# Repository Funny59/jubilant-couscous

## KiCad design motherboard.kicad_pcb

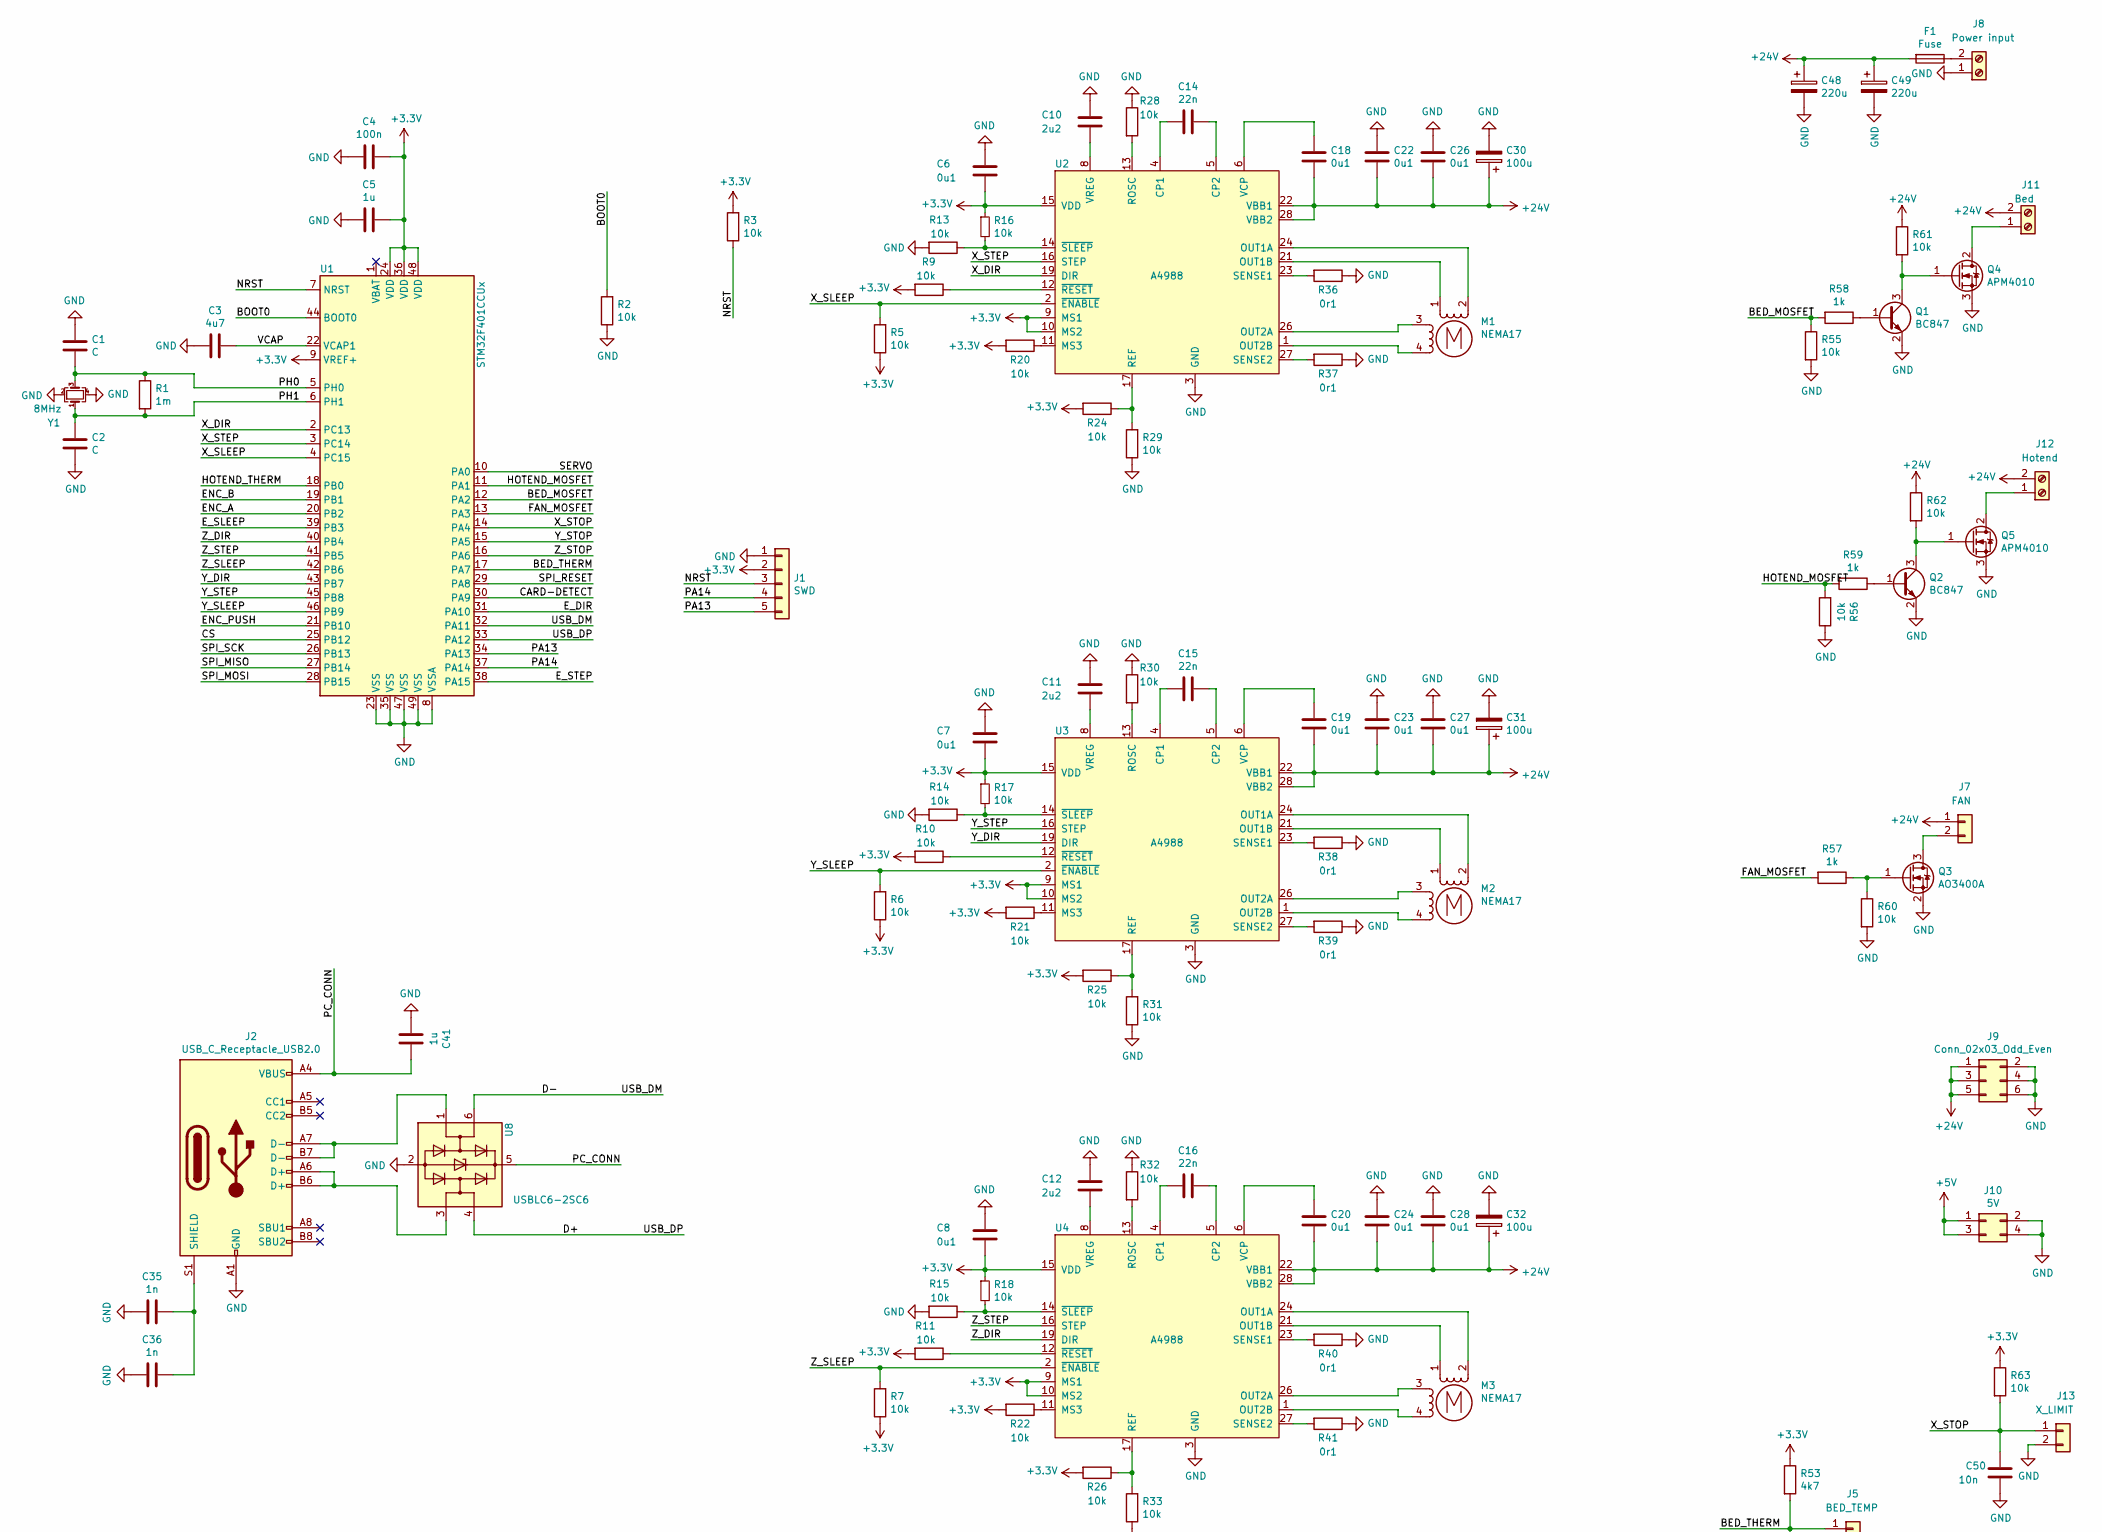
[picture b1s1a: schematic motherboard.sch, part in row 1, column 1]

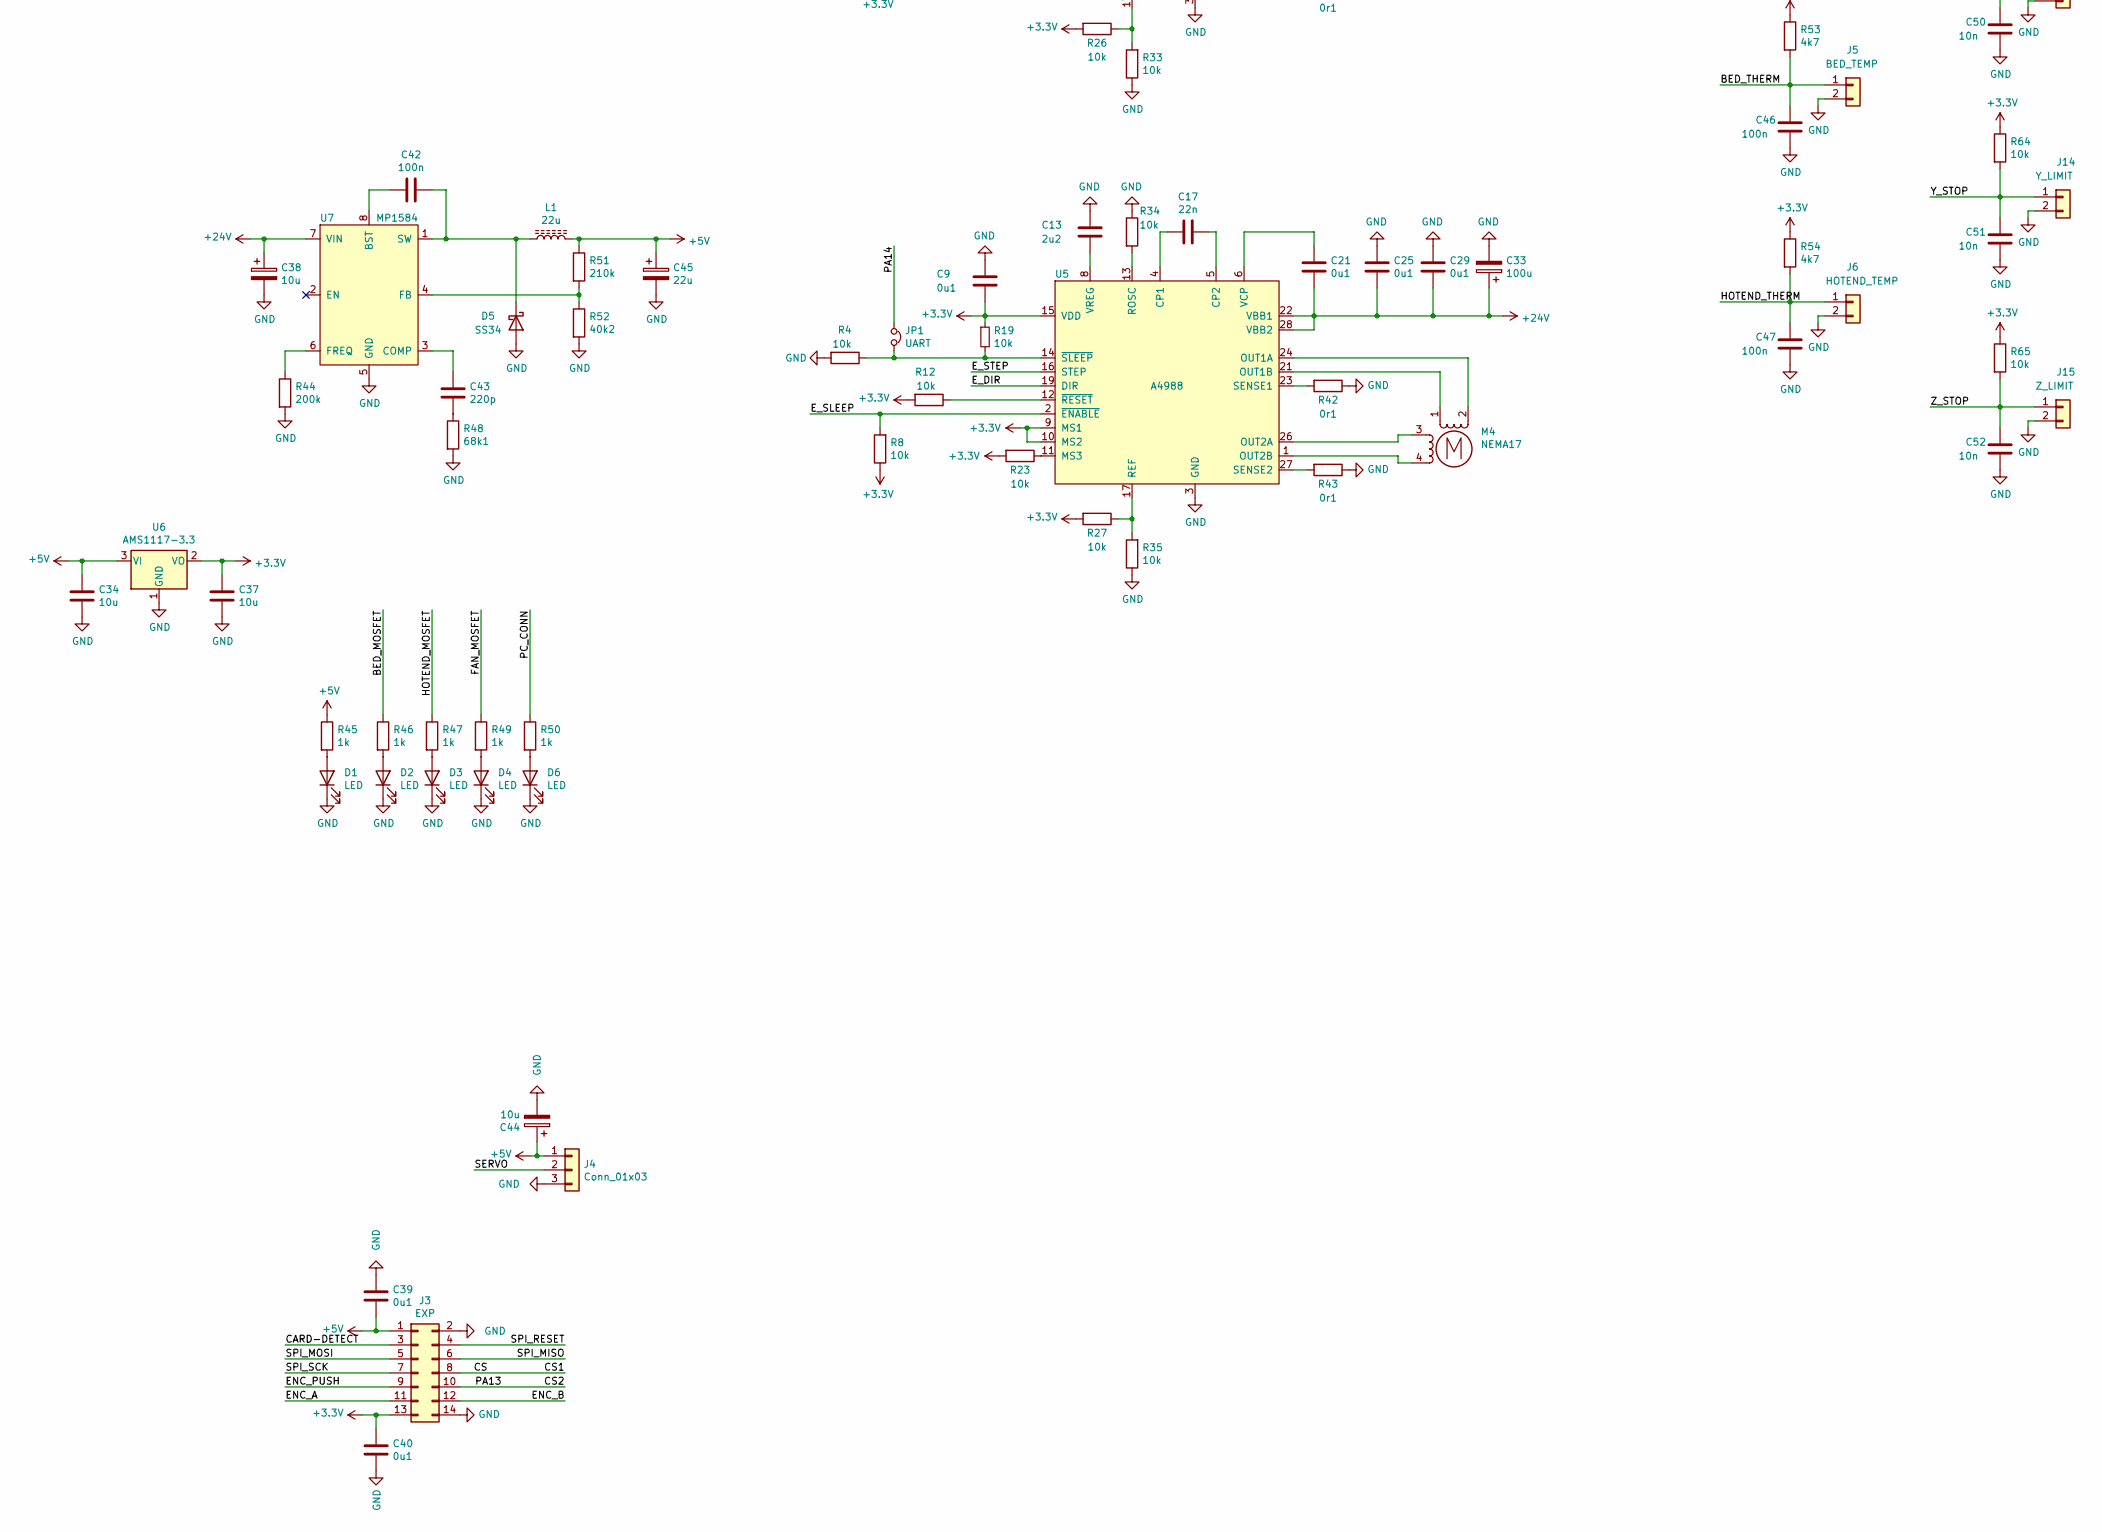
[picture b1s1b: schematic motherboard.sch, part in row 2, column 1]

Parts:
C1, C2: C; C_0603_1608Metric_Pad1.08x0.95mm_HandSolder
C3: 4u7; C_0603_1608Metric_Pad1.08x0.95mm_HandSolder
C4, C42, C46, C47: 100n; C_0603_1608Metric_Pad1.08x0.95mm_HandSolder
C5, C41: 1u; C_0603_1608Metric_Pad1.08x0.95mm_HandSolder
C6, C7, C8, C9, C18, C19, C20, C21, C22, C23, C24, C25, C26, C27, C28, C29, C39, C40: 0u1; C_0603_1608Metric_Pad1.08x0.95mm_HandSolder
C10, C11, C12, C13: 2u2; C_0603_1608Metric_Pad1.08x0.95mm_HandSolder
C14, C15, C16, C17: 22n; C_0603_1608Metric_Pad1.08x0.95mm_HandSolder
C30, C31, C32, C33: 100u; CP_Radial_D8.0mm_P3.50mm
C34, C37: 10u; C_0805_2012Metric_Pad1.18x1.45mm_HandSolder
C35, C36: 1n; C_0603_1608Metric_Pad1.08x0.95mm_HandSolder
C38, C44: 10u; CP_EIA-3528-21_Kemet-B_Pad1.50x2.35mm_HandSolder
C43: 220p; C_0603_1608Metric_Pad1.08x0.95mm_HandSolder
C45: 22u; CP_EIA-3528-21_Kemet-B_Pad1.50x2.35mm_HandSolder
C48, C49: 220u; CP_Radial_D8.0mm_P3.50mm
C50, C51, C52: 10n; C_0603_1608Metric_Pad1.08x0.95mm_HandSolder
D1, D2, D3, D4, D6: LED; LED_0603_1608Metric_Pad1.05x0.95mm_HandSolder
D5: SS34; D_SMA-SMB_Universal_Handsoldering
F1: Fuse; Fuse_Blade_Mini_directSolder
J1: SWD; PinHeader_1x05_P2.54mm_Vertical
J2: USB_C_Receptacle_USB2.0; USB_C_Receptacle_Palconn_UTC16-G
J3: EXP; IDC-Header_2x07_P2.54mm_Vertical
J4: Conn_01x03; JST_XH_B3B-XH-A_1x03_P2.50mm_Vertical
J5: BED_TEMP; JST_XH_B2B-XH-A_1x02_P2.50mm_Vertical
J6: HOTEND_TEMP; JST_XH_B2B-XH-A_1x02_P2.50mm_Vertical
J7: FAN; JST_XH_B2B-XH-A_1x02_P2.50mm_Vertical
J8: Power input; TerminalBlock_bornier-2_P5.08mm
J9: Conn_02x03_Odd_Even; PinHeader_2x03_P2.54mm_Vertical
J10: 5V; PinHeader_2x02_P2.54mm_Vertical
J11: Bed; TerminalBlock_bornier-2_P5.08mm
J12: Hotend; TerminalBlock_bornier-2_P5.08mm
J13: X_LIMIT; JST_XH_B2B-XH-A_1x02_P2.50mm_Vertical
J14: Y_LIMIT; JST_XH_B2B-XH-A_1x02_P2.50mm_Vertical
J15: Z_LIMIT; JST_XH_B2B-XH-A_1x02_P2.50mm_Vertical
JP1: UART; SolderJumper-2_P1.3mm_Open_TrianglePad1.0x1.5mm
L1: 22u; SDR0604
M1, M2, M3, M4: NEMA17; JST_XH_B4B-XH-A_1x04_P2.50mm_Vertical
Q1, Q2: BC847; SOT-23
Q3: AO3400A; SOT-23
Q4, Q5: APM4010; TO-252-2
R1: 1m; R_0603_1608Metric_Pad0.98x0.95mm_HandSolder
R2, R3, R24, R25, R26, R27, R55, R56, R60, R61, R62, R63, R64, R65: 10k; R_0603_1608Metric_Pad0.98x0.95mm_HandSolder
R4, R5, R6, R7, R8, R9, R10, R11, R12, R13, R14, R15, R16, R17, R18, R19, R20, R21, R22, R23, R28, R30, R32, R34: 10k; R_0402_1005Metric_Pad0.72x0.64mm_HandSolder
R29, R31, R33, R35: 10k; Potentiometer_Bourns_TC33X_Vertical
R36, R37, R38, R39, R40, R41, R42, R43: 0r1; R_1206_3216Metric_Pad1.30x1.75mm_HandSolder
R44: 200k; R_0603_1608Metric_Pad0.98x0.95mm_HandSolder
R45, R46, R47, R49, R50, R57, R58, R59: 1k; R_0603_1608Metric_Pad0.98x0.95mm_HandSolder
R48: 68k1; R_0603_1608Metric_Pad0.98x0.95mm_HandSolder
R51: 210k; R_0603_1608Metric_Pad0.98x0.95mm_HandSolder
R52: 40k2; R_0603_1608Metric_Pad0.98x0.95mm_HandSolder
R53, R54: 4k7; R_0603_1608Metric_Pad0.98x0.95mm_HandSolder
U1: STM32F401CCUx; QFN-48-1EP_7x7mm_P0.5mm_EP5.6x5.6mm
U2, U3, U4, U5: A4988; QFN-28-1EP_5x5mm_P0.5mm_EP3.35x3.35mm_ThermalVias
U6: AMS1117-3.3; SOT-223-3_TabPin2
U7: MP1584; SOIC-8-1EP_3.9x4.9mm_P1.27mm_EP2.29x3mm_ThermalVias
U8: USBLC6-2SC6; SOT-23-6
Y1: 8MHz; Crystal_SMD_3225-4Pin_3.2x2.5mm

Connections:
+3V3: C4.1, C5.1, C6.2, C7.2, C8.2, C9.2, C37.1, C40.2, J1.2, J3.13, R3.2, R5.1, R6.1, R7.1, R8.1, R9.2, R10.2, R11.2, R12.2, R16.1, R17.1, R18.1, R19.1, R20.2, R21.2, R22.2, R23.2, R24.2, R25.2, R26.2, R27.2, R53.1, R54.1, R63.1, R64.1, R65.1, U1.9 (VREF+), U1.24 (VDD), U1.36 (VDD), U1.48 (VDD), U2.9 (MS1), U2.10 (MS2), U2.15 (VDD), U3.9 (MS1), U3.10 (MS2), U3.15 (VDD), U4.9 (MS1), U4.10 (MS2), U4.15 (VDD), U5.9 (MS1), U5.10 (MS2), U5.15 (VDD), U6.2 (VO)
+5V: C34.1, C39.1, C44.1, C45.1, J3.1, J4.1, J10.1, J10.3, L1.2, R45.1, R51.1, U6.3 (VI)
+24V: C18.1, C19.1, C20.1, C21.1, C22.1, C23.1, C24.1, C25.1, C26.1, C27.1, C28.1, C29.1, C30.1, C31.1, C32.1, C33.1, C38.1, C48.1, C49.1, F1.2, J7.1, J9.1, J9.3, J9.5, J11.2, J12.2, R61.1, R62.1, U2.22 (VBB1), U2.28 (VBB2), U3.22 (VBB1), U3.28 (VBB2), U4.22 (VBB1), U4.28 (VBB2), U5.22 (VBB1), U5.28 (VBB2), U7.7 (VIN); also elsewhere on the board
/BED_MOSFET: R46.1, R55.1, R58.2, U1.12 (PA2)
/BED_THERM: C46.1, J5.1, R53.2, U1.17 (PA7)
/BOOT0: R2.2, U1.44 (BOOT0)
/CARD-DETECT: J3.3, U1.30 (PA9)
/CS: J3.8, U1.25 (PB12)
/CS2: J1.5, J3.10, U1.34 (PA13)
/D+: U1.33 (PA12), U8.4 (I/O2)
/D-: U1.32 (PA11), U8.6 (I/O1)
/ENC_A: J3.11, U1.20 (PB2)
/ENC_B: J3.12, U1.19 (PB1)
/ENC_PUSH: J3.9, U1.21 (PB10)
/E_DIR: U1.31 (PA10), U5.19 (DIR)
/E_SLEEP: R8.2, U1.39 (PB3), U5.2 (~ENABLE)
/E_STEP: U1.38 (PA15), U5.16 (STEP)
/FAN_MOSFET: R49.1, R57.2, U1.13 (PA3)
/HOTEND_MOSFET: R47.1, R56.2, R59.2, U1.11 (PA1)
/HOTEND_THERM: C47.1, J6.1, R54.2, U1.18 (PB0)
/NRST: J1.3, R3.1, U1.7 (NRST)
/PA14: J1.4, JP1.1, U1.37 (PA14)
/PC_CONN: C41.1, J2.A4 (VBUS), J2.A9 (VBUS), J2.B4 (VBUS), J2.B9 (VBUS), R50.1, U8.5 (VBUS)
/PH0: C1.2, R1.1, U1.5 (PH0), Y1.3
/PH1: C2.1, R1.2, U1.6 (PH1), Y1.1
/SERVO: J4.2, U1.10 (PA0)
/SPI_MISO: J3.6, U1.27 (PB14)
/SPI_MOSI: J3.5, U1.28 (PB15)
/SPI_RESET: J3.4, U1.29 (PA8)
/SPI_SCK: J3.7, U1.26 (PB13)
/VCAP: C3.1, U1.22 (VCAP1)
/X_DIR: U1.2 (PC13), U2.19 (DIR)
/X_SLEEP: R5.2, U1.4 (PC15), U2.2 (~ENABLE)
/X_STEP: U1.3 (PC14), U2.16 (STEP)
/X_STOP: C50.1, J13.1, R63.2, U1.14 (PA4)
/Y_DIR: U1.43 (PB7), U3.19 (DIR)
/Y_SLEEP: R6.2, U1.46 (PB9), U3.2 (~ENABLE)
/Y_STEP: U1.45 (PB8), U3.16 (STEP)
/Y_STOP: C51.1, J14.1, R64.2, U1.15 (PA5)
/Z_DIR: U1.40 (PB4), U4.19 (DIR)
/Z_SLEEP: R7.2, U1.42 (PB6), U4.2 (~ENABLE)
/Z_STEP: U1.41 (PB5), U4.16 (STEP)
/Z_STOP: C52.1, J15.1, R65.2, U1.16 (PA6)
GND: C1.1, C2.2, C3.2, C4.2, C5.2, C6.1, C7.1, C8.1, C9.1, C10.1, C11.1, C12.1, C13.1, C22.2, C23.2, C24.2, C25.2, C26.2, C27.2, C28.2, C29.2, C30.2, C31.2, C32.2, C33.2, C34.2, C35.2, C36.2, C37.2, C38.2, C39.2, C40.1, C41.2, C44.2, C45.2, C46.2, C47.2, C48.2, C49.2, C50.2, C51.2, C52.2, D1.1 (K), D2.1 (K), D3.1 (K), D4.1 (K), D5.2 (A), D6.1 (K), J1.1, J2.A1 (GND), J2.A12 (GND), J2.B1 (GND), J2.B12 (GND), J3.2, J3.14, J4.3, J5.2, J6.2, J8.1, J9.2, J9.4, J9.6, J10.2, J10.4, J13.2, J14.2, J15.2, Q1.2 (E), Q2.2 (E), Q3.2 (S), Q4.3 (S), Q5.3 (S), R2.1, R4.2, R13.2, R14.2, R15.2, R28.1, R29.1, R30.1, R31.1, R32.1, R33.1, R34.1, R35.1, R36.1, R37.1, R38.1, R39.1, R40.1, R41.1, R42.1, R43.1, R44.2, R48.2, R52.2, R55.2, R56.1, R60.2, U1.8 (VSSA), U1.23 (VSS), U1.35 (VSS), U1.47 (VSS), U1.49 (VSS), U2.3 (GND), U2.18 (GND), U2.29 (GND), U3.3 (GND), U3.18 (GND), U3.29 (GND), U4.3 (GND), U4.18 (GND), U4.29 (GND), U5.3 (GND), U5.18 (GND), U5.29 (GND), U6.1 (GND), U7.5 (GND), U8.2 (GND), Y1.2, Y1.4; also elsewhere on the board
unnamed: C10.2, U2.8 (VREG)
unnamed: C11.2, U3.8 (VREG)
unnamed: C12.2, U4.8 (VREG)
unnamed: C13.2, U5.8 (VREG)
unnamed: C14.1, U2.5 (CP2)
unnamed: C14.2, U2.4 (CP1)
unnamed: C15.1, U3.5 (CP2)
unnamed: C15.2, U3.4 (CP1)
unnamed: C16.1, U4.5 (CP2)
unnamed: C16.2, U4.4 (CP1)
unnamed: C17.1, U5.5 (CP2)
unnamed: C17.2, U5.4 (CP1)
unnamed: C18.2, U2.6 (VCP)
unnamed: C19.2, U3.6 (VCP)
unnamed: C20.2, U4.6 (VCP)
unnamed: C21.2, U5.6 (VCP)
unnamed: C35.1, C36.1, J2.S1 (SHIELD)
unnamed: C42.1, D5.1 (K), L1.1, U7.1 (SW)
unnamed: C42.2, U7.8 (BST)
unnamed: C43.1, R48.1
unnamed: C43.2, U7.3 (COMP)
unnamed: D1.2 (A), R45.2
unnamed: D2.2 (A), R46.2
unnamed: D3.2 (A), R47.2
unnamed: D4.2 (A), R49.2
unnamed: D6.2 (A), R50.2
unnamed: F1.1, J8.2
unnamed: J2.A6 (D+), J2.B6 (D+), U8.3 (I/O2)
unnamed: J2.A7 (D-), J2.B7 (D-), U8.1 (I/O1)
unnamed: J7.2, Q3.3 (D)
unnamed: J11.1, Q4.2 (D)
unnamed: J12.1, Q5.2 (D)
unnamed: JP1.2, R4.1, R19.2, U5.14 (~SLEEP)
unnamed: M1.1, U2.21 (OUT1B)
unnamed: M1.2 (-), U2.24 (OUT1A)
unnamed: M1.3, U2.26 (OUT2A)
unnamed: M1.4, U2.1 (OUT2B)
unnamed: M2.1, U3.21 (OUT1B)
unnamed: M2.2 (-), U3.24 (OUT1A)
unnamed: M2.3, U3.26 (OUT2A)
unnamed: M2.4, U3.1 (OUT2B)
unnamed: M3.1, U4.21 (OUT1B)
unnamed: M3.2 (-), U4.24 (OUT1A)
unnamed: M3.3, U4.26 (OUT2A)
unnamed: M3.4, U4.1 (OUT2B)
unnamed: M4.1, U5.21 (OUT1B)
unnamed: M4.2 (-), U5.24 (OUT1A)
unnamed: M4.3, U5.26 (OUT2A)
unnamed: M4.4, U5.1 (OUT2B)
unnamed: Q1.1 (B), R58.1
unnamed: Q1.3 (C), Q4.1 (G), R61.2
unnamed: Q2.1 (B), R59.1
unnamed: Q2.3 (C), Q5.1 (G), R62.2
unnamed: Q3.1 (G), R57.1, R60.1
unnamed: R9.1, U2.12 (~RESET)
unnamed: R10.1, U3.12 (~RESET)
unnamed: R11.1, U4.12 (~RESET)
unnamed: R12.1, U5.12 (~RESET)
unnamed: R13.1, R16.2, U2.14 (~SLEEP)
unnamed: R14.1, R17.2, U3.14 (~SLEEP)
unnamed: R15.1, R18.2, U4.14 (~SLEEP)
unnamed: R20.1, U2.11 (MS3)
unnamed: R21.1, U3.11 (MS3)
unnamed: R22.1, U4.11 (MS3)
unnamed: R23.1, U5.11 (MS3)
unnamed: R24.1, R29.2, U2.17 (REF)
unnamed: R25.1, R31.2, U3.17 (REF)
unnamed: R26.1, R33.2, U4.17 (REF)
unnamed: R27.1, R35.2, U5.17 (REF)
unnamed: R28.2, U2.13 (ROSC)
unnamed: R30.2, U3.13 (ROSC)
unnamed: R32.2, U4.13 (ROSC)
unnamed: R34.2, U5.13 (ROSC)
unnamed: R36.2, U2.23 (SENSE1)
unnamed: R37.2, U2.27 (SENSE2)
unnamed: R38.2, U3.23 (SENSE1)
unnamed: R39.2, U3.27 (SENSE2)
unnamed: R40.2, U4.23 (SENSE1)
unnamed: R41.2, U4.27 (SENSE2)
unnamed: R42.2, U5.23 (SENSE1)
unnamed: R43.2, U5.27 (SENSE2)
unnamed: R44.1, U7.6 (FREQ~)
unnamed: R51.2, R52.1, U7.4 (FB)

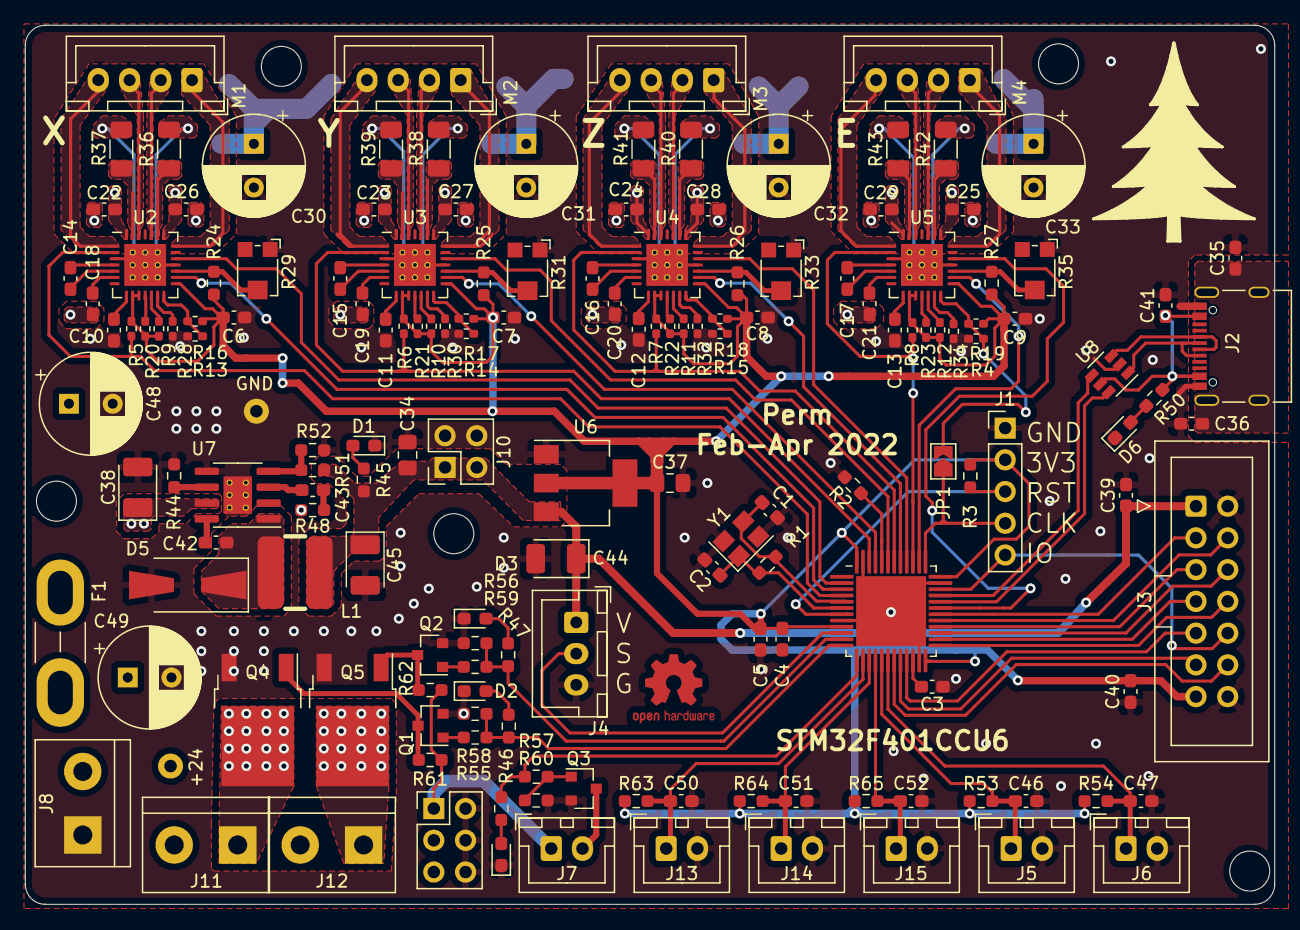
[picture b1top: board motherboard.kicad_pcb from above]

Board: 2 copper layers, 100.0 x 70.3 mm, 162 parts (1 on the bottom side), 127 nets.

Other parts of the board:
GND: TestPoint_Loop_D1.80mm_Drill1.0mm_Beaded
GND#2: TestPoint_Loop_D1.80mm_Drill1.0mm_Beaded
QR*****: QR_signed

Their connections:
+24V: GND.1; also elsewhere on the board
GND: GND#2.1; also elsewhere on the board

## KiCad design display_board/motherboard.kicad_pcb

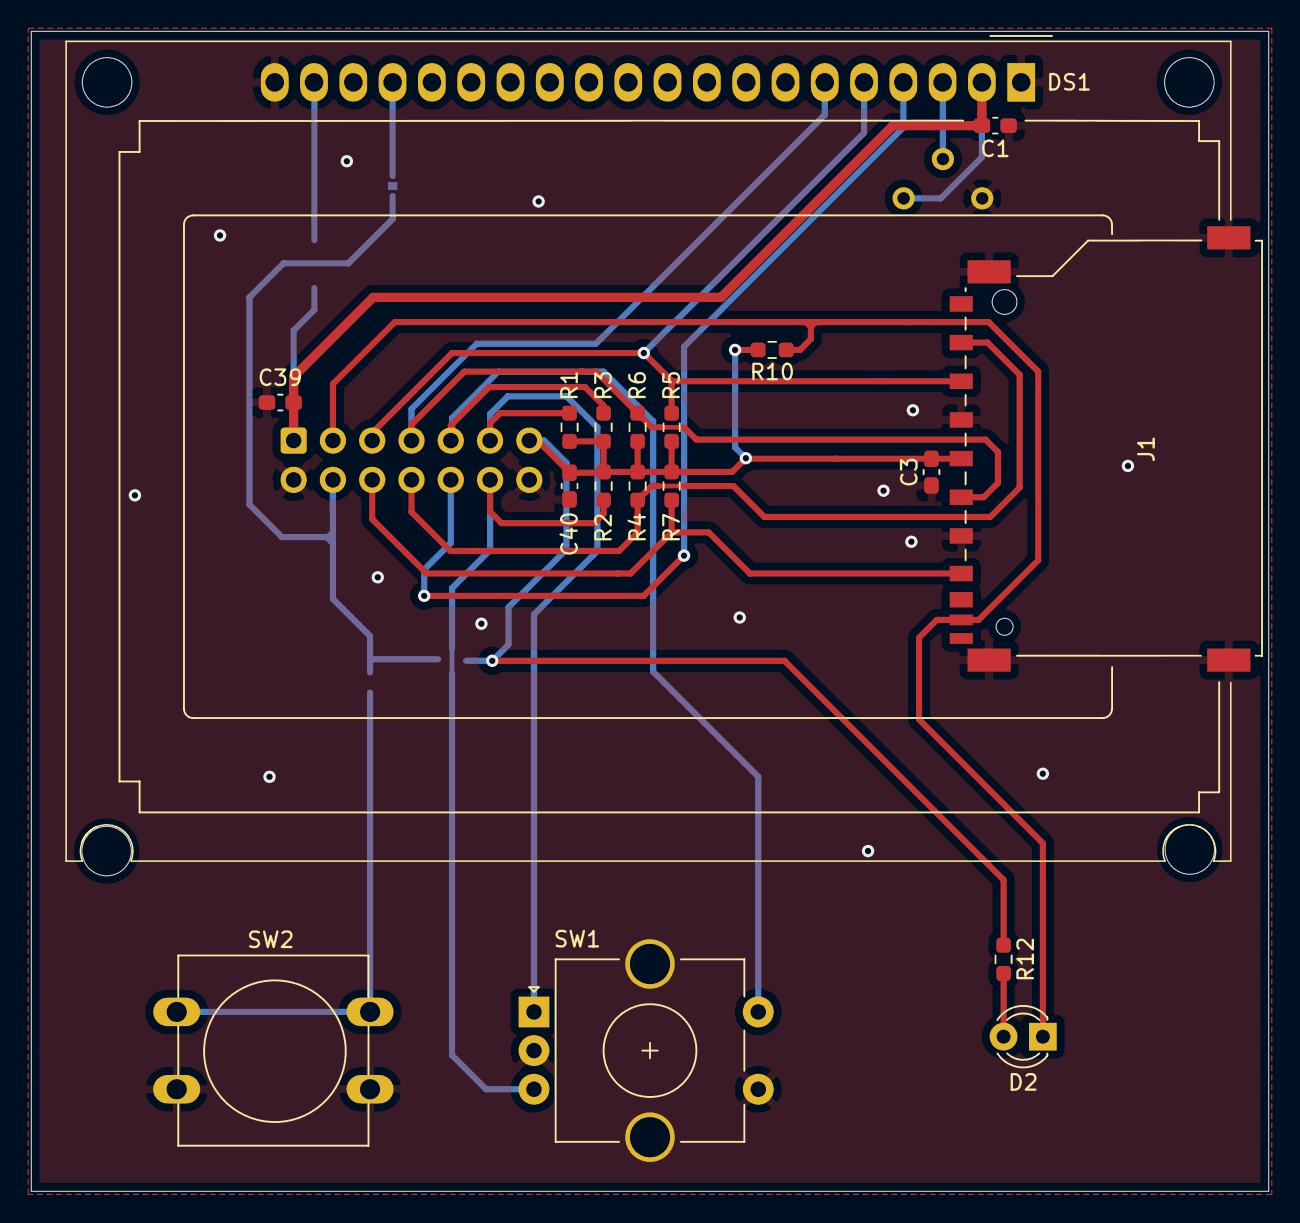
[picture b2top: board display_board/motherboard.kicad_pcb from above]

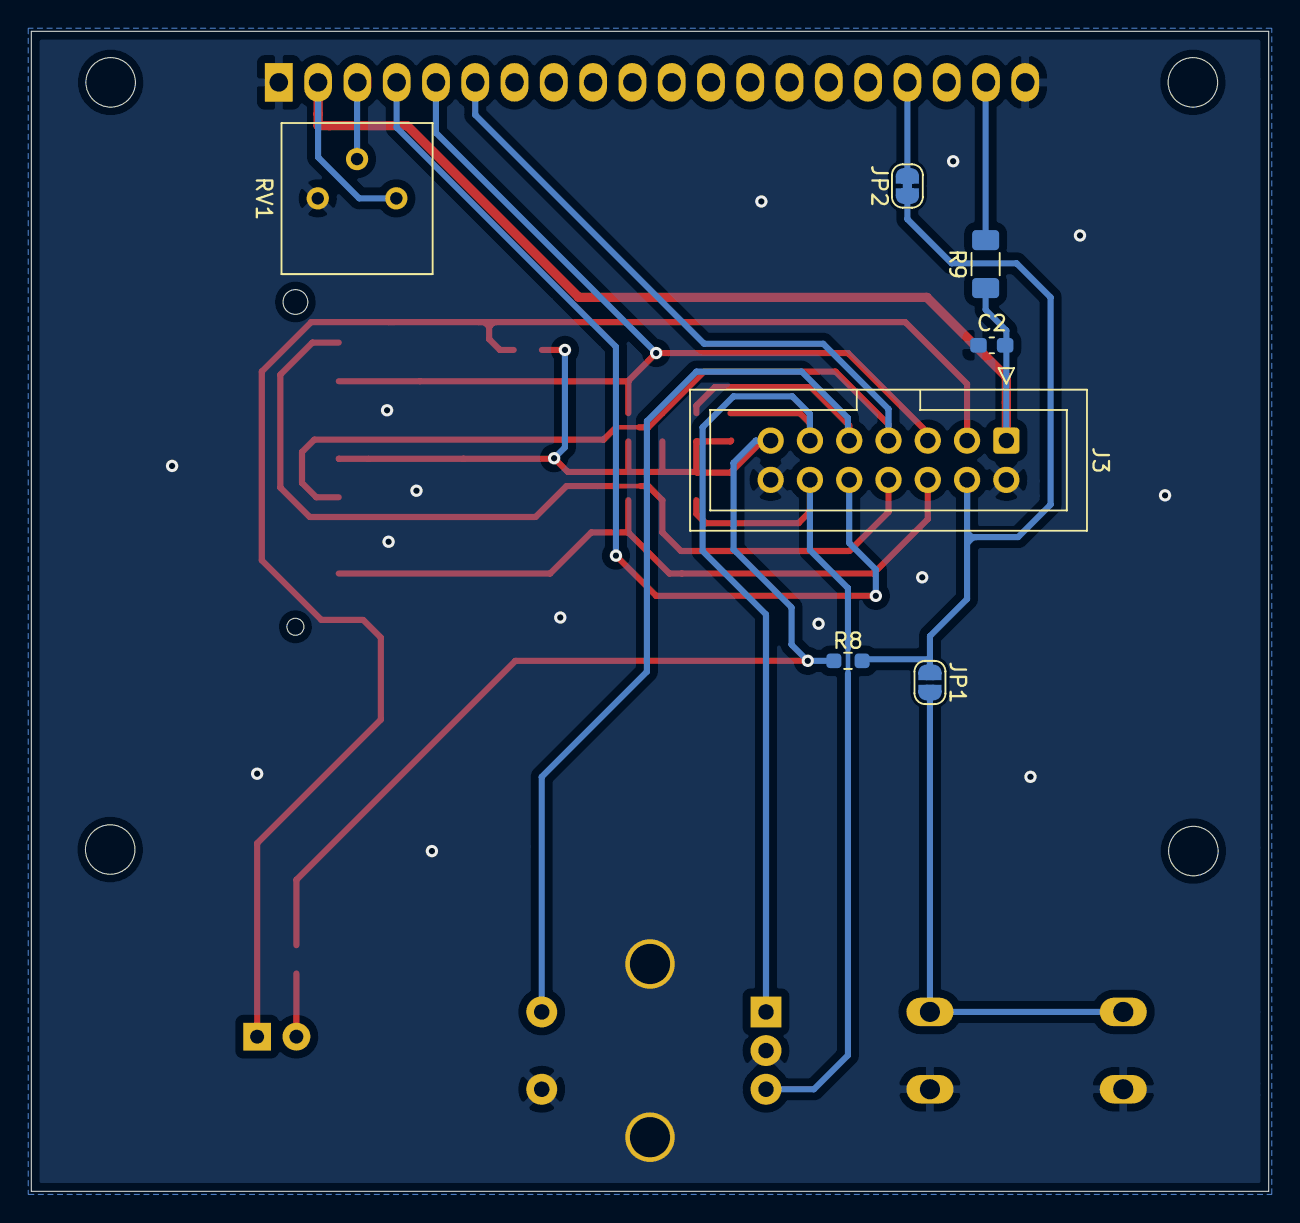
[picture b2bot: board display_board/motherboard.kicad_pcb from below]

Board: 2 copper layers, 80.0 x 75.0 mm, 25 parts (7 on the bottom side), 18 nets.

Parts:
C1, C2, C3, C39, C40: 0u1; C_0603_1608Metric_Pad1.08x0.95mm_HandSolder
D2: LED; LED_D3.0mm
DS1: LCD12864; AG12864E
J1: SD_Card; SD_TE_2041021
J3: EXP; IDC-Header_2x07_P2.54mm_Vertical
JP1: Jumper_NO_Small; SolderJumper-2_P1.3mm_Open_RoundedPad1.0x1.5mm
JP2: Jumper_NC_Small; SolderJumper-2_P1.3mm_Bridged_RoundedPad1.0x1.5mm
R1, R2, R3, R4, R5, R6, R7, R8, R10: 10k; R_0603_1608Metric_Pad0.98x0.95mm_HandSolder
R9: 470; R_1206_3216Metric_Pad1.30x1.75mm_HandSolder
R12: 470; R_0603_1608Metric_Pad0.98x0.95mm_HandSolder
RV1: 10k; Potentiometer_Bourns_3386P_Vertical
SW1: Rotary_Encoder_Switch; RotaryEncoder_Alps_EC11E-Switch_Vertical_H20mm_CircularMoun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
SW2: SW_Push; SW_PUSH-12mm

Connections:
+3V3: C3.2, C40.2, J1.4, J3.13, R1.2, R2.2, R3.1, R4.2, R5.2, R6.2, R7.2, R8.2, R10.2, R12.1
+5V: C1.1, C2.2, C39.1, DS1.2, J3.1, R9.1, RV1.1
/CARD-DETECT: D2.1, J1.10, J3.3, R10.1
/CS: J1.1, J3.8, R4.1
/CS2: DS1.4, J3.10
/ENC_A: J3.11, R1.1, SW1.A
/ENC_B: J3.12, R2.1, SW1.B
/ENC_PUSH: J3.9, R3.2, SW1.S2
/SPI_MISO: J1.7, J3.6, R7.1
/SPI_MOSI: DS1.5, J1.2, J3.5, R5.1
/SPI_RESET: J3.4, JP1.1, JP2.1, R8.1
/SPI_SCK: DS1.6, J1.5, J3.7, R6.1
GND: C1.2, C2.1, C3.1, C39.2, C40.1, DS1.1, DS1.20, J1.3, J1.6, J1.12, J3.2, J3.14, RV1.3, SW1.C, SW1.S1, SW2.2
unnamed: D2.2, R12.2
unnamed: DS1.3, RV1.2
unnamed: DS1.17, JP2.2
unnamed: DS1.19, R9.2
unnamed: JP1.2, SW2.1

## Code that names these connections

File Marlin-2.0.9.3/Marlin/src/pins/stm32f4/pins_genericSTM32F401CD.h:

#define FLASH_EEPROM_EMULATION //emulate a EEPROM 4Kb in flash

#define TEMP_0_PIN                          PB0
#define TEMP_BED_PIN                        PA7

#define HEATER_0_PIN                        PA1
#define HEATER_BED_PIN                      PA2
#define FAN_PIN                             PA3

#define X_STOP_PIN                          PA4
#define Y_STOP_PIN                          PA5
#define Z_STOP_PIN                          PA6

#define E0_STEP_PIN                         PA15
#define E0_DIR_PIN                          PA10
#define E0_ENABLE_PIN                       PB3

#define X_STEP_PIN                          PC14
#define X_DIR_PIN                           PC13
#define X_ENABLE_PIN                        PC15

#define Y_STEP_PIN                          PB8
#define Y_DIR_PIN                           PB7
#define Y_ENABLE_PIN                        PB9

#define Z_STEP_PIN                          PB5
#define Z_DIR_PIN                           PB4
#define Z_ENABLE_PIN                        PB6

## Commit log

2022-02-08 new pcb and fix schematic
2022-02-28 change connection from USB to UART to support STM32 without USB
2022-05-14 change PCB design
2022-05-15 add Marlin build
2022-05-22 add display board
2022-05-28 pcb fixes
2022-05-28 add todo
2022-05-28 add gitignore
2022-05-28 add logo to pcb
